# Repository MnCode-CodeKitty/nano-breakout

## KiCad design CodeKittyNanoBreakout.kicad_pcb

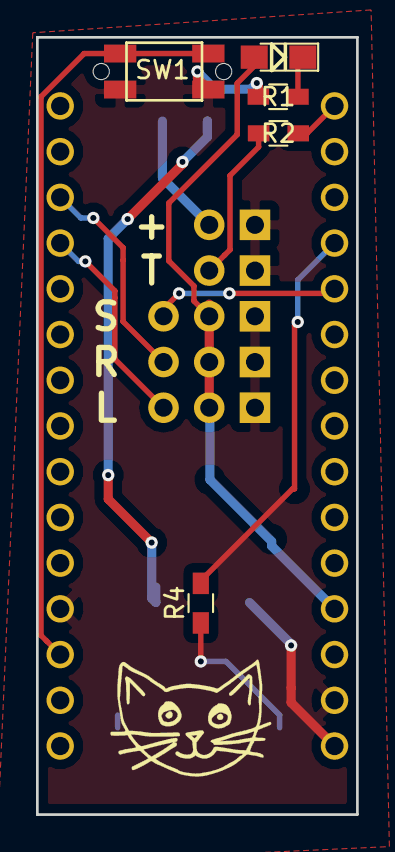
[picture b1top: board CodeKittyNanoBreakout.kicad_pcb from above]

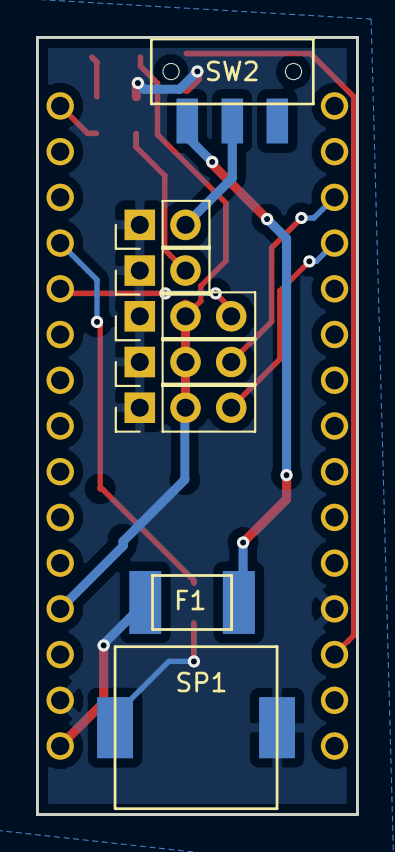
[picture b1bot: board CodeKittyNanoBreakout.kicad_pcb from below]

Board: 2 copper layers, 17.8 x 43.2 mm, 14 parts (9 on the bottom side), 14 nets.

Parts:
D1: LED; LED_0805_HandSoldering
F1: F_Small; DM_FUSE_PTC0ZCG
P1, P2: CONN_01X02; Pin_Header_Straight_1x02_Pitch2.54mm
P3, P4, P5: CONN_01X03; Pin_Header_Straight_1x03_Pitch2.54mm
R1, R2: R; R_0603_HandSoldering
R4: 1K; R_0603_HandSoldering
SP1: PIEZO; DM_PiezSMD_PMKCS0909E4000-R1
SW1: SW_PUSH_SMALL_H; DM_SMD_BUTTON_PTS810
SW2: Switch_SPDT_x2; DM_SPDT_RTAngle_JS102011SAQN
U1: ArduinoNano

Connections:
5V: D1.2, P3.2, P4.2, P5.2, U1.27
BUZZ: R4.2, U1.19
GND: P1.1, P2.1, P3.1, P4.1, P5.1, R1.2, SP1.2, SW1.2, U1.4, U1.29
LSERVO: P3.3, U1.12
unnamed: D1.1, R1.1
unnamed: F1.1, SW2.3
unnamed: P1.2, SW2.2
unnamed: P2.2, R2.1
unnamed: R4.1, SP1.1
RSERVO: P4.3, U1.13
RST: SW1.1, U1.3
SENS: P5.3, U1.20
TAIL: R2.2, U1.16
VCC: F1.2, U1.30

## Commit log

2017-10-15 subrepo created
2017-10-15 added custom libs
2018-02-04 changed DM to CK
2018-02-04 "fixed a broke thing"
2018-02-04 fixy brokey more
2018-02-04 1.0.2
2018-02-20 removed driver from piezo -- direct drive baby!
